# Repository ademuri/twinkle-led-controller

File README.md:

ESP32-based controller board which drives up to 10 strings of "twinkle" LED
fairy lights. These are strings of LEDs where half of the string is wired with
one polarity, and the other half with opposite polarity, so that one half or the
other (alternating down the string) can be lit up separately.

Work in progress.

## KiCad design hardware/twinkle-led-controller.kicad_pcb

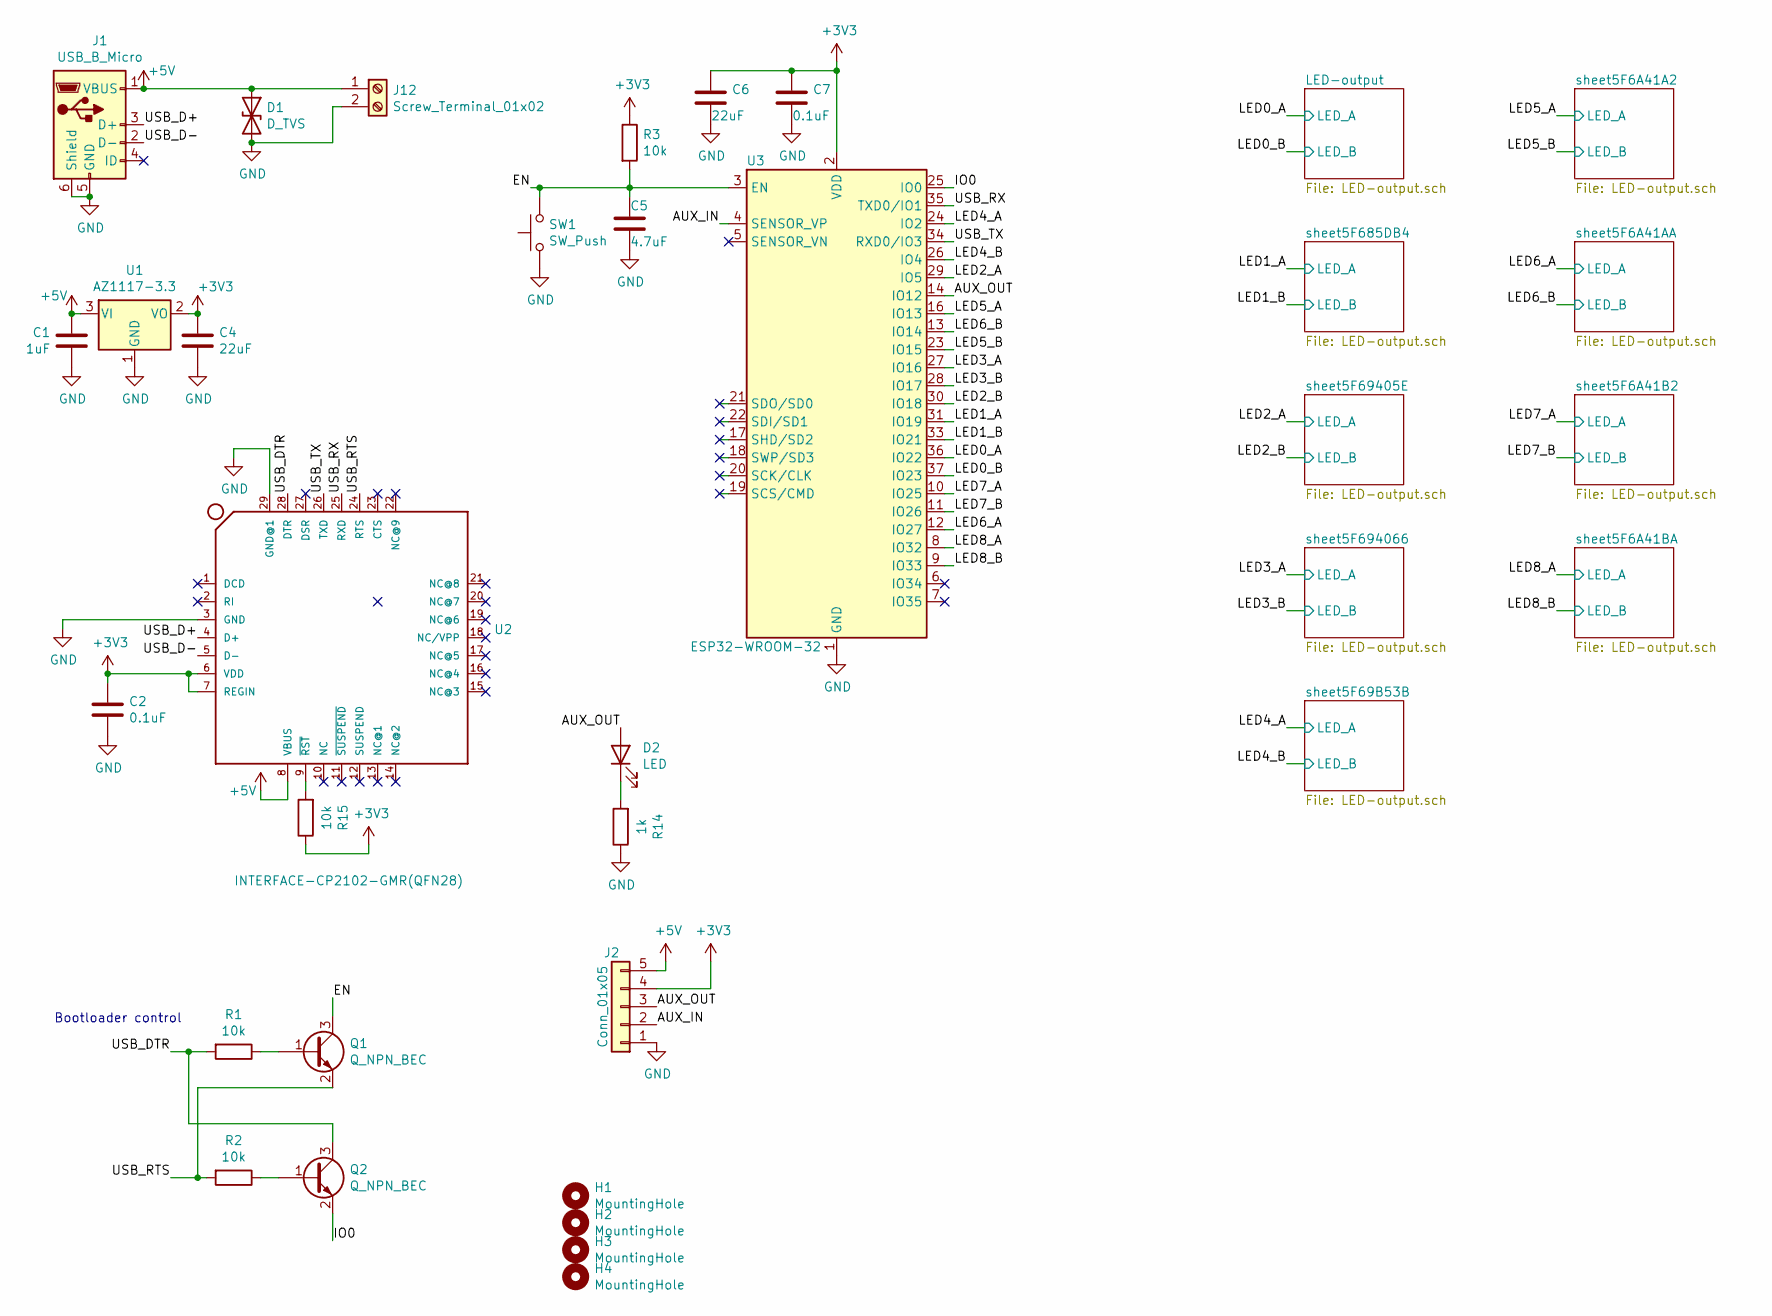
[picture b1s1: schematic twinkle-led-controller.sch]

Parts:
C1: 1uF; C_0402_1005Metric; LCSC C52923
C2, C7: 0.1uF; C_0402_1005Metric; LCSC C1525
C4, C6: 22uF; C_0603_1608Metric; LCSC C59461
C5: 4.7uF; C_0603_1608Metric; LCSC C19666
D1: D_TVS; D_SMB; LCSC C78395
D2: LED; LED_0603_1608Metric; LCSC C2286
H1, H2, H3, H4: MountingHole; HOLE_M4
J1: USB_B_Micro; FRAMATOME_10118194-0001LF_fixed_bridges
J2: Conn_01x05; PinHeader_1x05_P2.54mm_Vertical
J12: Screw_Terminal_01x02; Wurth_ScrewTerminal_1x02_P5.00mm_691137710002
Q1, Q2: Q_NPN_BEC; SOT-23; LCSC C2150
R1, R2, R3, R15: 10k; R_0402_1005Metric; LCSC C25744
R14: 1k; R_0402_1005Metric; LCSC C11702
SW1: SW_Push; SW_TACTILE_5.1MM_TS-1187A-C-D-B; LCSC C318888
U1: AZ1117-3.3; SOT-223; LCSC C6186
U2: INTERFACE-CP2102-GMR(QFN28); QFN28G_0.5-5X5MM; LCSC C6568
U3: ESP32-WROOM-32

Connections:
+3V3: C2.1, C4.1, C6.1, C7.1, J2.4, R3.1, R15.1, U1.2 (VO), U2.6 (VDD), U2.7 (REGIN), U3.2 (VDD)
+5V: C1.2, D1.1 (A1), J1.1 (VBUS), J2.5, J12.1, U1.3 (VI), U2.8 (VBUS); also elsewhere on the board
/AUX_IN: J2.2, U3.4 (SENSOR_VP)
/AUX_OUT: D2.2 (A), J2.3, U3.14 (IO12)
/EN: C5.1, Q1.3 (C), R3.2, SW1.2, U3.3 (EN)
/IO0: Q2.2 (E), U3.25 (IO0)
/LED0_A: U3.36 (IO22); also elsewhere on the board
/LED0_B: U3.37 (IO23); also elsewhere on the board
/LED1_A: U3.31 (IO19); also elsewhere on the board
/LED1_B: U3.33 (IO21); also elsewhere on the board
/LED2_A: U3.29 (IO5); also elsewhere on the board
/LED2_B: U3.30 (IO18); also elsewhere on the board
/LED3_A: U3.27 (IO16); also elsewhere on the board
/LED3_B: U3.28 (IO17); also elsewhere on the board
/LED4_A: U3.24 (IO2); also elsewhere on the board
/LED4_B: U3.26 (IO4); also elsewhere on the board
/LED5_A: U3.16 (IO13); also elsewhere on the board
/LED5_B: U3.23 (IO15); also elsewhere on the board
/LED6_A: U3.12 (IO27); also elsewhere on the board
/LED6_B: U3.13 (IO14); also elsewhere on the board
/LED7_A: U3.10 (IO25); also elsewhere on the board
/LED7_B: U3.11 (IO26); also elsewhere on the board
/LED8_A: U3.8 (IO32); also elsewhere on the board
/LED8_B: U3.9 (IO33); also elsewhere on the board
/USB_D+: J1.3 (D+), U2.4 (D+)
/USB_D-: J1.2 (D-), U2.5 (D-)
/USB_DTR: Q2.3 (C), R1.2, U2.28 (DTR)
/USB_RTS: Q1.2 (E), R2.2, U2.24 (RTS)
/USB_RX: U2.25 (RXD), U3.35 (TXD0/IO1)
/USB_TX: U2.26 (TXD), U3.34 (RXD0/IO3)
GND: C1.1, C2.2, C4.2, C5.2, C6.2, C7.2, D1.2 (A2), J1.5 (GND), J1.6 (Shield), J2.1, J12.2, R14.1, SW1.1, U1.1 (GND), U2.3 (GND), U2.29 (GND@1), U3.1 (GND), U3.15 (GND), U3.38 (GND), U3.39 (GND); also elsewhere on the board
unnamed: D2.1 (K), R14.2
unnamed: Q1.1 (B), R1.1
unnamed: Q2.1 (B), R2.1
unnamed: R15.2, U2.9 (~RST~)

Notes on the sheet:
Bootloader control

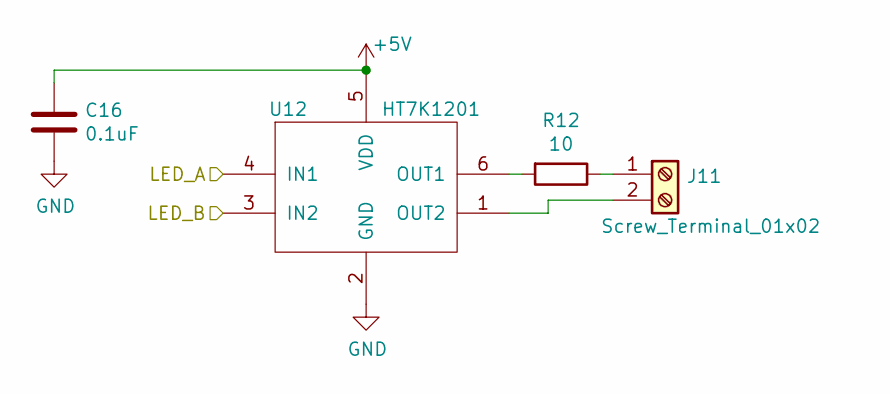
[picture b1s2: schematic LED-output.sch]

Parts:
C8: 0.1uF; C_0402_1005Metric; LCSC C1525
J3: Screw_Terminal_01x02; Wurth_ScrewTerminal_1x02_P5.00mm_691137710002
R4: 10; R_1206_3216Metric; LCSC C17903
U4: HT7K1201; SOT-23-6; LCSC C182041

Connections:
+5V: C8.1, U4.5 (VDD); also elsewhere on the board
/LED0_A: U4.4 (IN1); also elsewhere on the board
/LED0_B: U4.3 (IN2); also elsewhere on the board
GND: C8.2, U4.2 (GND); also elsewhere on the board
unnamed: J3.1, R4.1
unnamed: J3.2, U4.1 (OUT2)
unnamed: R4.2, U4.6 (OUT1)

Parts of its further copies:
C9, C10, C11, C12, C13, C14, C15, C16, C17: 0.1uF; C_0402_1005Metric; LCSC C1525
J4, J5, J6, J7, J8, J9, J10, J11: Screw_Terminal_01x02; Wurth_ScrewTerminal_1x02_P5.00mm_691137710002
R5, R6, R7, R8, R9, R10, R11, R12, R13: 10; R_1206_3216Metric; LCSC C17903
U5, U6, U7, U8, U9, U10, U11, U12, U13: HT7K1201; SOT-23-6; LCSC C182041

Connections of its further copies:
+5V: C9.1, C10.1, C11.1, C12.1, C13.1, C14.1, C15.1, C16.1, U5.5 (VDD), U6.5 (VDD), U7.5 (VDD), U8.5 (VDD), U9.5 (VDD), U10.5 (VDD), U11.5 (VDD), U12.5 (VDD); also elsewhere on the board
/LED1_A: U5.4 (IN1); also elsewhere on the board
/LED1_B: U5.3 (IN2); also elsewhere on the board
/LED2_A: U6.4 (IN1); also elsewhere on the board
/LED2_B: U6.3 (IN2); also elsewhere on the board
/LED3_A: U7.4 (IN1); also elsewhere on the board
/LED3_B: U7.3 (IN2); also elsewhere on the board
/LED4_A: U8.4 (IN1); also elsewhere on the board
/LED4_B: U8.3 (IN2); also elsewhere on the board
/LED5_A: U9.4 (IN1); also elsewhere on the board
/LED5_B: U9.3 (IN2); also elsewhere on the board
/LED6_A: U10.4 (IN1); also elsewhere on the board
/LED6_B: U10.3 (IN2); also elsewhere on the board
/LED7_A: U11.4 (IN1); also elsewhere on the board
/LED7_B: U11.3 (IN2); also elsewhere on the board
/LED8_A: U12.4 (IN1); also elsewhere on the board
/LED8_B: U12.3 (IN2); also elsewhere on the board
GND: C9.2, C10.2, C11.2, C12.2, C13.2, C14.2, C15.2, C16.2, U5.2 (GND), U6.2 (GND), U7.2 (GND), U8.2 (GND), U9.2 (GND), U10.2 (GND), U11.2 (GND), U12.2 (GND); also elsewhere on the board
unnamed: J4.1, R5.1
unnamed: J4.2, U5.1 (OUT2)
unnamed: J5.1, R6.1
unnamed: J5.2, U6.1 (OUT2)
unnamed: J6.1, R7.1
unnamed: J6.2, U7.1 (OUT2)
unnamed: J7.1, R8.1
unnamed: J7.2, U8.1 (OUT2)
unnamed: J8.1, R9.1
unnamed: J8.2, U9.1 (OUT2)
unnamed: J9.1, R10.1
unnamed: J9.2, U10.1 (OUT2)
unnamed: J10.1, R11.1
unnamed: J10.2, U11.1 (OUT2)
unnamed: J11.1, R12.1
unnamed: J11.2, U12.1 (OUT2)
unnamed: R5.2, U5.6 (OUT1)
unnamed: R6.2, U6.6 (OUT1)
unnamed: R7.2, U7.6 (OUT1)
unnamed: R8.2, U8.6 (OUT1)
unnamed: R9.2, U9.6 (OUT1)
unnamed: R10.2, U10.6 (OUT1)
unnamed: R11.2, U11.6 (OUT1)
unnamed: R12.2, U12.6 (OUT1)

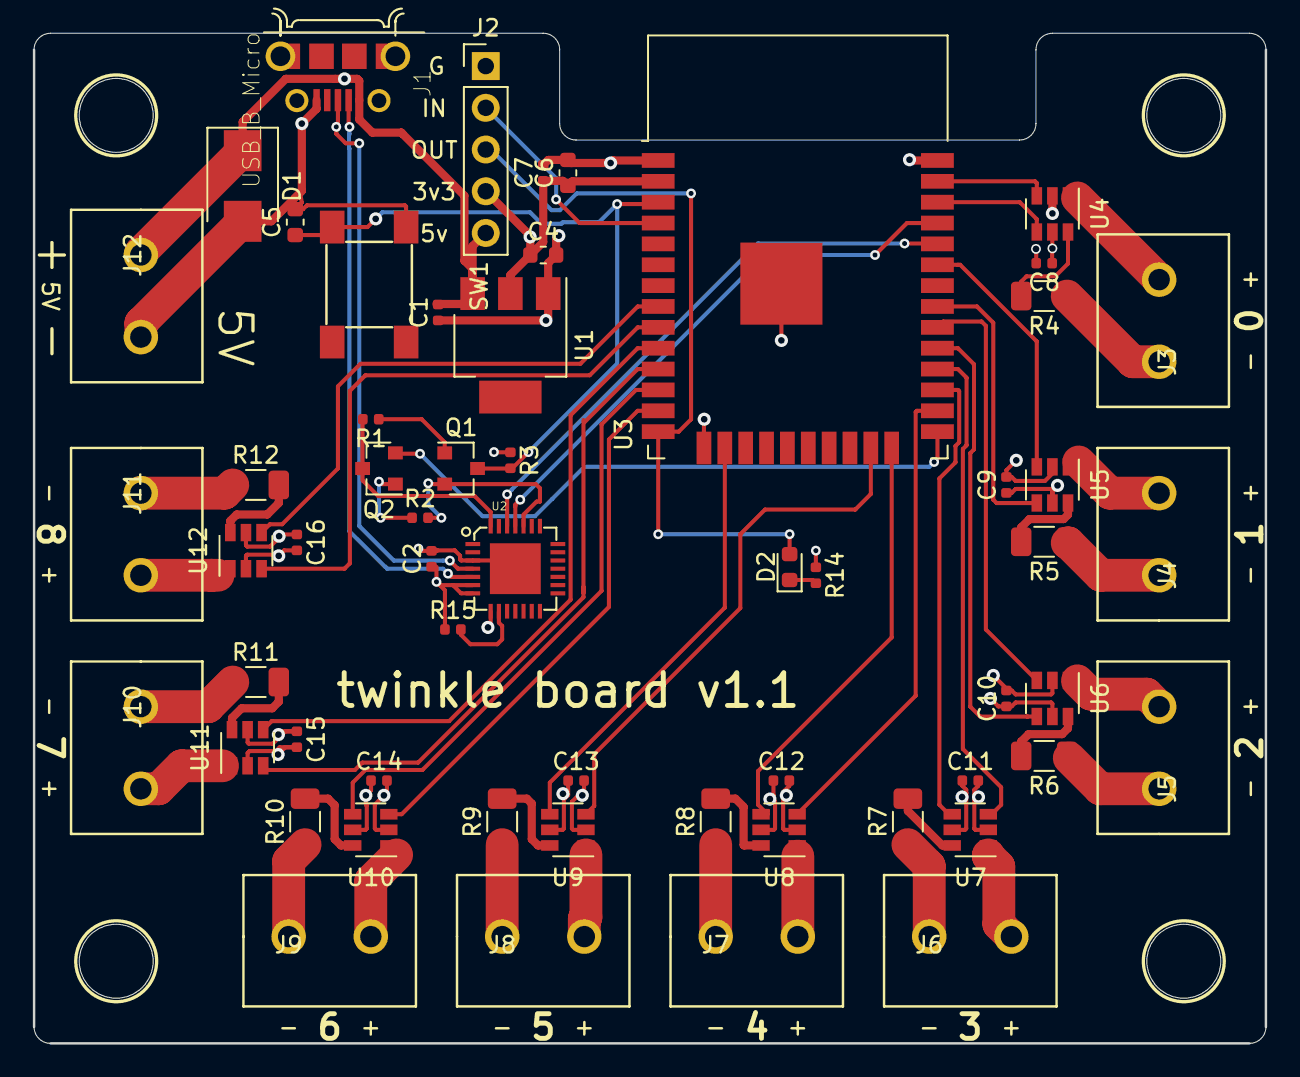
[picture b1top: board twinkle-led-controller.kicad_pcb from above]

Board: 4 copper layers, 75.0 x 61.4 mm, 62 parts (0 on the bottom side), 62 nets.

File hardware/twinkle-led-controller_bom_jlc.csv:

"Comment","Designator","Footprint","LCSC Part #"
"1uF","C1","C_0402_1005Metric","C52923"
"0.1uF","C2,C7,C8,C9,C10,C11,C12,C13,C14,C15,C16","C_0402_1005Metric","C1525"
"22uF","C4,C6","C_0603_1608Metric","C59461"
"4.7uF","C5","C_0603_1608Metric","C19666"
"D_TVS","D1","D_SMB","C78395"
"LED","D2","LED_0603_1608Metric","C2286"
"Q_NPN_BEC","Q1,Q2","SOT-23","C2150"
"10k","R2,R1,R3,R15","R_0402_1005Metric","C25744"
"10","R4,R5,R6,R7,R8,R9,R10,R11,R12","R_1206_3216Metric","C17903"
"1k","R14","R_0402_1005Metric","C11702"
"SW_Push","SW1","SW_TACTILE_5.1MM_TS-1187A-C-D-B","C318888"
"AZ1117-3.3","U1","SOT-223","C6186"
"INTERFACE-CP2102-GMR(QFN28)","U2","QFN28G_0.5-5X5MM","C6568"
"HT7K1201","U4,U5,U6,U7,U8,U9,U10,U11,U12","SOT-23-6","C182041"

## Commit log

2020-08-23 First pass at schematic
2020-08-23 Add footprints
2020-08-25 Layout v1.0
2020-08-25 Fix v1.0 layout and generate gerbers/placement files
    - Update to CP2102, since JLCPCB doesn't have CP2104
    - Fix current-limiting resistors to 10 ohm
2020-09-01 Add initial software - just a basic web server
2020-09-05 Add PWM control for lights
2020-09-09 Add metadata
2020-09-14 Hardware revision 1.1:
    - Fix pins to not use flash pins
    - Fix screw terminal footprint (holes were too small)
    - Add screw terminal for power
    - Add out for multi-unit synchronization
2020-09-15 Switch to using hardware PWM peripheral.
    This increases the effective PWM frequency to 10kHz.
2020-10-04 Blink LED during boot
2020-10-06 Disable the PWM interrupt during OTA (fixes OTA)
2020-10-06 Increase OTA timeout to 5s, to decrease flakiness
2020-10-24 Add the reset reason to the dashboard.
2020-11-08 Set strands and add UI.
2020-11-15 Remove MDNS periodic refresh
    This isn't needed in most cases, and causes random reboots at uptimes of
    ~1 day. Note: I originally added this to work around MDNS issues with
    Mikrotik routers.
2020-11-15 Add support for MQTT light control with Home Assistant
2020-11-15 Add support for effects and brightness
2020-11-15 Fix LED glitches.
    Glitches were caused by reusing PWM timer when switching it between
    pins. This changes the first 8 strands to use platform support for PWM
    (note: some are hardware and some are software). The last strand is
    driven via a bit-banging interrupt.
2020-11-16 Reduce glitchiness.
    This moves to having a single interrupt for both LEDC PWM and manual
    PWM. It runs the interrupt very frequently (100kHz), and only updates
    one half of one LEDC strand every interrupt. It updates the manual PWM
    strand every interrupt.
2020-11-19 Add MQTT username and password
2020-11-21 Make twinkle alternate every other strand
2020-11-29 Reconect to MQTT on disconnect
2021-01-02 Vary brightness across strands
